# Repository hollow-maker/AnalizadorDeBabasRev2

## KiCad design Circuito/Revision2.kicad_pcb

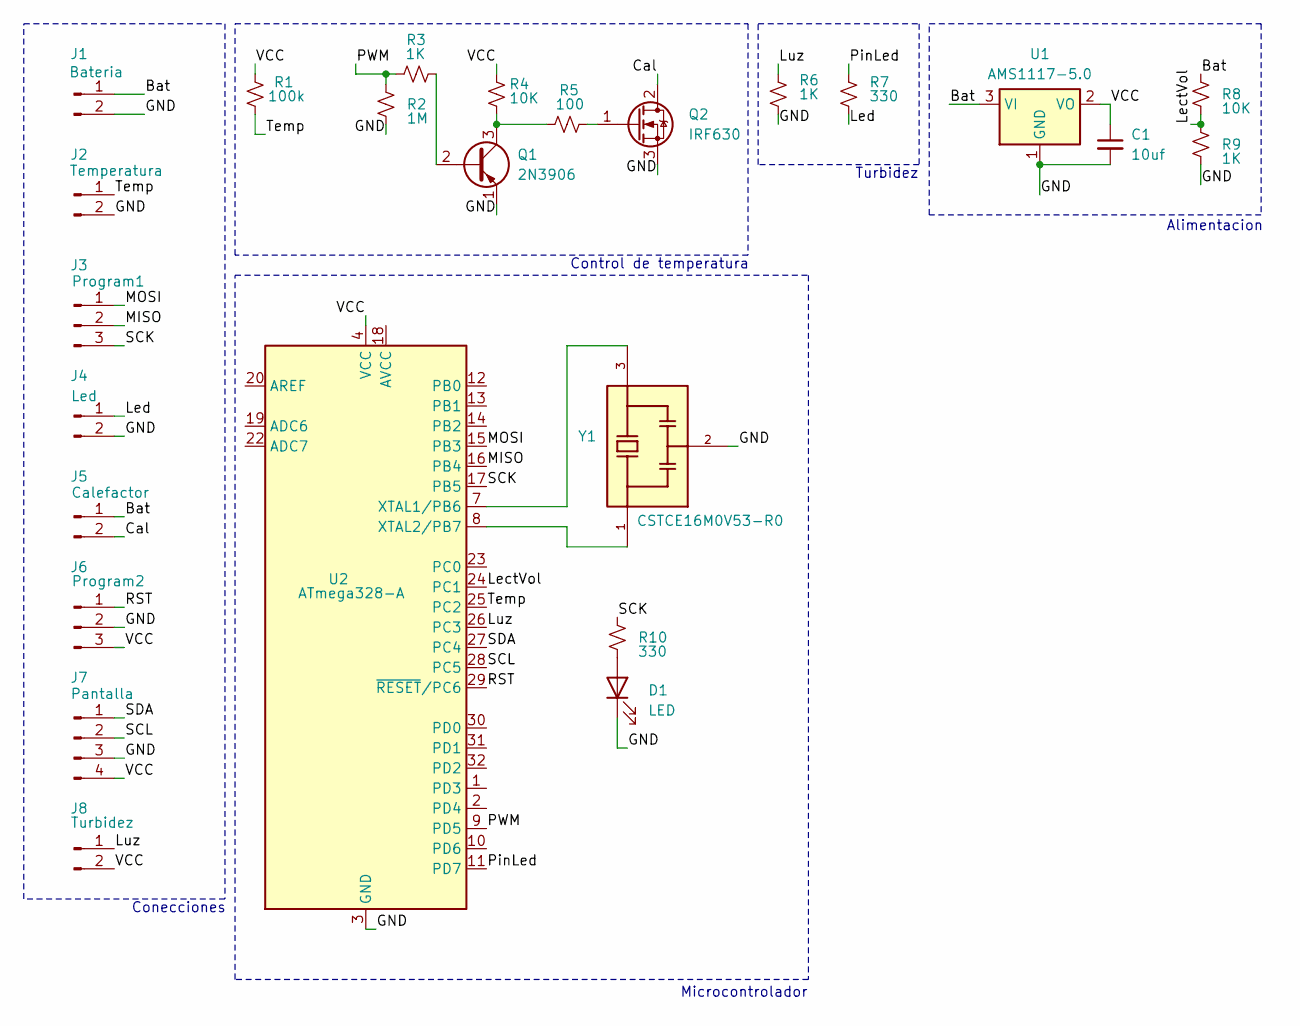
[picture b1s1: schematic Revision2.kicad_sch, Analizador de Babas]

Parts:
C1: 10uf; RES_ERA3A_0603_PAN-L
D1: LED; RES_ERA3A_0603_PAN-L
J1: Bateria; PinHeader_1x02_P2.54mm_Vertical
J2: Temperatura; PinHeader_1x02_P2.54mm_Vertical
J3: Program1; PinHeader_1x03_P2.54mm_Vertical
J4: Led; PinHeader_1x02_P2.54mm_Vertical
J5: Calefactor; PinHeader_1x02_P2.54mm_Vertical
J6: Program2; PinHeader_1x03_P2.54mm_Vertical
J7: Pantalla; PinHeader_1x04_P2.54mm_Vertical
J8: Turbidez; PinHeader_1x02_P2.54mm_Vertical
Q1: 2N3906; TO-92_Inline
Q2: IRF630; TO-220-3_Vertical
R1: 100k; RES_ERA3A_0603_PAN-L
R2: 1M; RES_ERA3A_0603_PAN-L
R3, R6, R9: 1K; RES_ERA3A_0603_PAN-L
R4, R8: 10K; RES_ERA3A_0603_PAN-L
R5: 100; RES_ERA3A_0603_PAN-L
R7, R10: 330; RES_ERA3A_0603_PAN-L
U1: AMS1117-5.0; SOT-223-3_TabPin2
U2: ATmega328-A; TQFP-32_7x7mm_P0.8mm
Y1: CSTCE16M0V53-R0; Resonator_SMD_Murata_CSTxExxV-3Pin_3.0x1.1mm; PARTREV 10/24/2022

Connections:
/Bat: J1.1, J5.1, R8.1, U1.3 (VI)
/Cal: J5.2, Q2.2 (D)
/GND: C1.2, D1.1 (K), J1.2, J2.2, J4.2, J6.2, J7.3, Q1.1 (E), Q2.3 (S), R2.2, R6.2, R9.2, U1.1 (GND), U2.3 (GND), U2.5 (GND), U2.21 (GND), Y1.2
/LectVol: R8.2, R9.1, U2.24 (PC1)
/Led: J4.1, R7.2
/Luz: J8.1, R6.1, U2.26 (PC3)
/MISO: J3.2, U2.16 (PB4)
/MOSI: J3.1, U2.15 (PB3)
/PWM: R2.1, R3.1, U2.9 (PD5)
/PinLed: R7.1, U2.11 (PD7)
/RST: J6.1, U2.29 (~RESET/PC6)
/SCK: J3.3, R10.1, U2.17 (PB5)
/SCL: J7.2, U2.28 (PC5)
/SDA: J7.1, U2.27 (PC4)
/Temp: J2.1, R1.2, U2.25 (PC2)
/VCC: C1.1, J6.3, J7.4, J8.2, R1.1, R4.1, U1.2 (VO), U2.4 (VCC), U2.6 (VCC)
unnamed: D1.2 (A), R10.2
unnamed: Q1.2 (B), R3.2
unnamed: Q1.3 (C), R4.2, R5.1
unnamed: Q2.1 (G), R5.2
unnamed: U2.7 (XTAL1/PB6), Y1.3
unnamed: U2.8 (XTAL2/PB7), Y1.1

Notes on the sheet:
Microcontrolador
Alimentacion
Conecciones
Control de temperatura
Turbidez

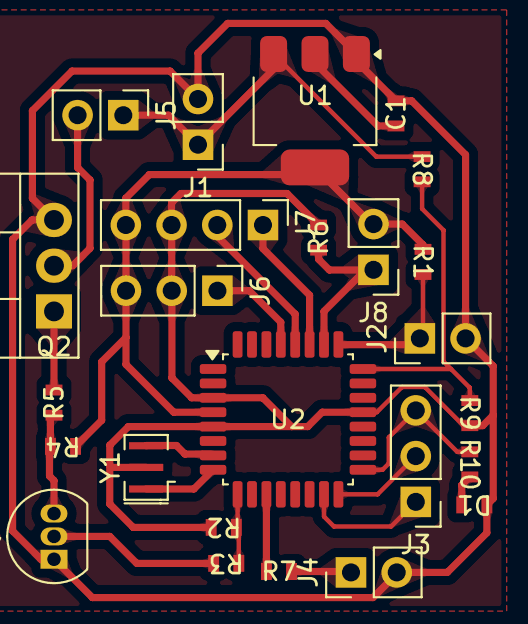
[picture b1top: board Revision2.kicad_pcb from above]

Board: 2 copper layers, 25 parts (0 on the bottom side), 22 nets.
